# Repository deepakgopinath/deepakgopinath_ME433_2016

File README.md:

# deepakgopinath_ME433_2016
Repository for ME433 - Advanced Mechatronics Course (Spring 2016).

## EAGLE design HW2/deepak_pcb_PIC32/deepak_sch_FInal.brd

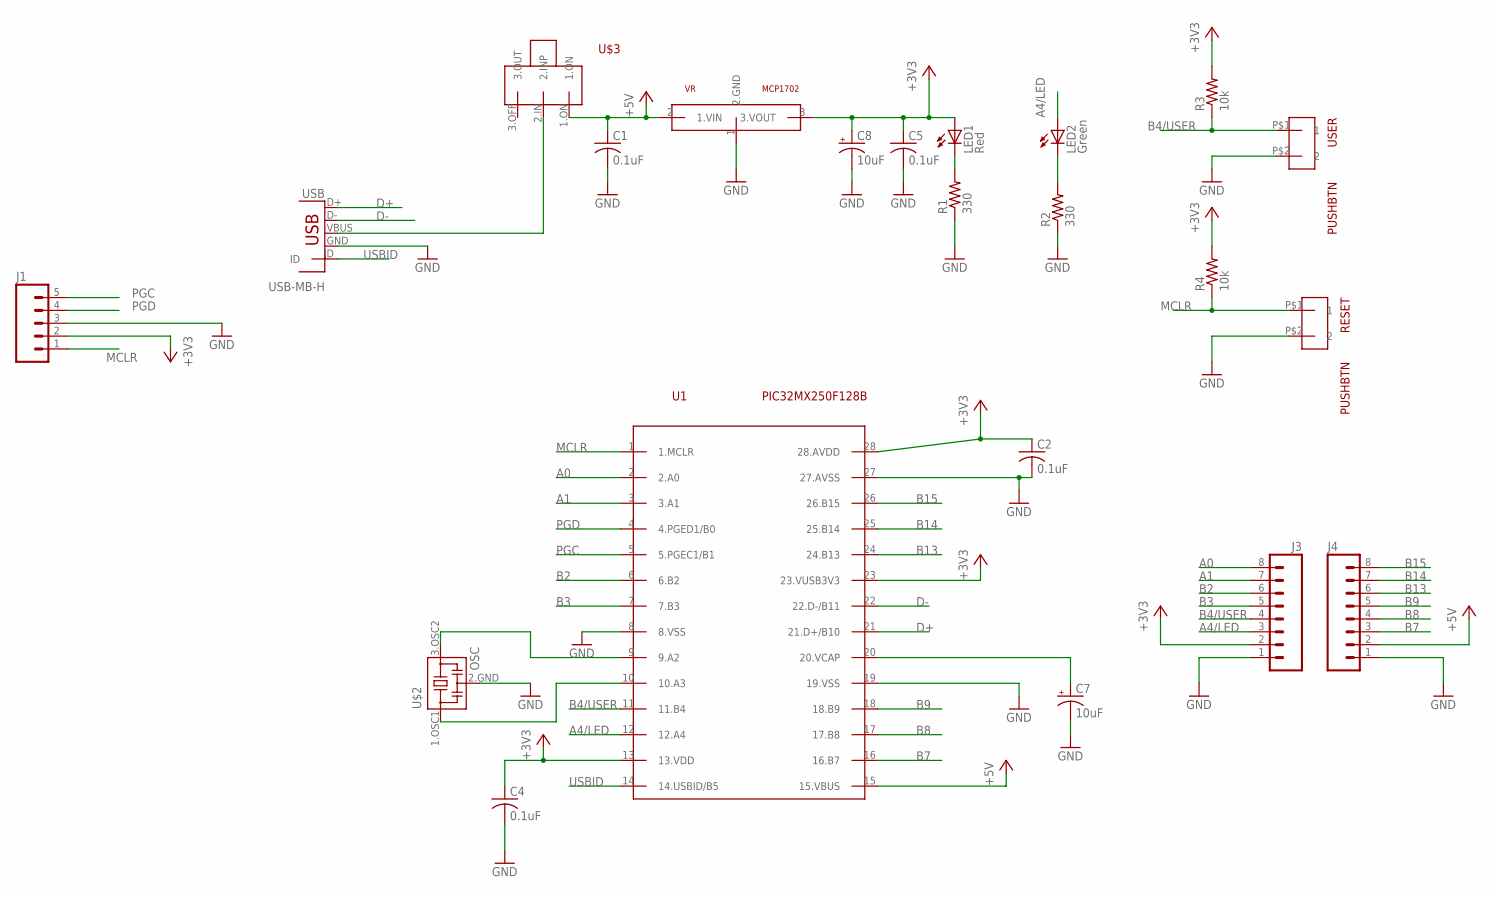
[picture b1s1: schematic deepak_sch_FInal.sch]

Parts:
C1, C2, C4, C5: 0.1uF; C025-024X044
C7, C8: 10uF; B45181A
J1: M05PTH; 1X05
J3, J4: M08; 1X08_ROUND
LED1: Red; LED3MM
LED2: Green; LED3MM
R1, R2: 330; 0207/10
R3, R4: 10k; 0207/10
RESET: PUSHBTN
U1: PIC32MX250F128B; DIL28-3
U$2: OSC
U$3: SLIDESWITCH
USB: USB-MB-H
USER: PUSHBTN
VR: MCP1702; TO92

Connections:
+3V3: C2.1, C4.1, C5.1, C8.+, J1.2, J3.2, LED1.A, R3.2, R4.2, U1.13 (13.VDD), U1.23 (23.VUSB3V3), U1.28 (28.AVDD), VR.3 (3.VOUT)
+5V: C1.1, J4.2, U1.15 (15.VBUS), U$3.1.ON, VR.2 (1.VIN)
A0: J3.8, U1.2 (2.A0)
A1: J3.7, U1.3 (3.A1)
A4/LED: J3.3, LED2.A, U1.12 (12.A4)
B2: J3.6, U1.6 (6.B2)
B3: J3.5, U1.7 (7.B3)
B4/USER: J3.4, R3.1, U1.11 (11.B4), USER.P$1 (1)
B7: J4.3, U1.16 (16.B7)
B8: J4.4, U1.17 (17.B8)
B9: J4.5, U1.18 (18.B9)
B13: J4.6, U1.24 (24.B13)
B14: J4.7, U1.25 (25.B14)
B15: J4.8, U1.26 (26.B15)
D+: U1.21 (21.D+/B10), USB.D+
D-: U1.22 (22.D-/B11), USB.D-
GND: C1.2, C2.2, C4.2, C5.2, C7.-, C8.-, J1.3, J3.1, J4.1, R1.1, R2.1, RESET.P$2 (2), U1.8 (8.VSS), U1.19 (19.VSS), U1.27 (27.AVSS), U$2.2.GND (2), USB.GND, USER.P$2 (2), VR.1 (2.GND)
MCLR: J1.1, R4.1, RESET.P$1 (1), U1.1 (1.MCLR)
unnamed: U1.9 (9.A2), U$2.3.OSC2 (3)
unnamed: U1.10 (10.A3), U$2.1.OSC1 (1)
unnamed: U$3.2.IN (2.INP), USB.VBUS
unnamed: LED2.K (C), R2.2
unnamed: LED1.K (C), R1.2
unnamed: C7.+, U1.20 (20.VCAP)
PGC: J1.5, U1.5 (5.PGEC1/B1)
PGD: J1.4, U1.4 (4.PGED1/B0)
USBID: U1.14 (14.USBID/B5), USB.ID

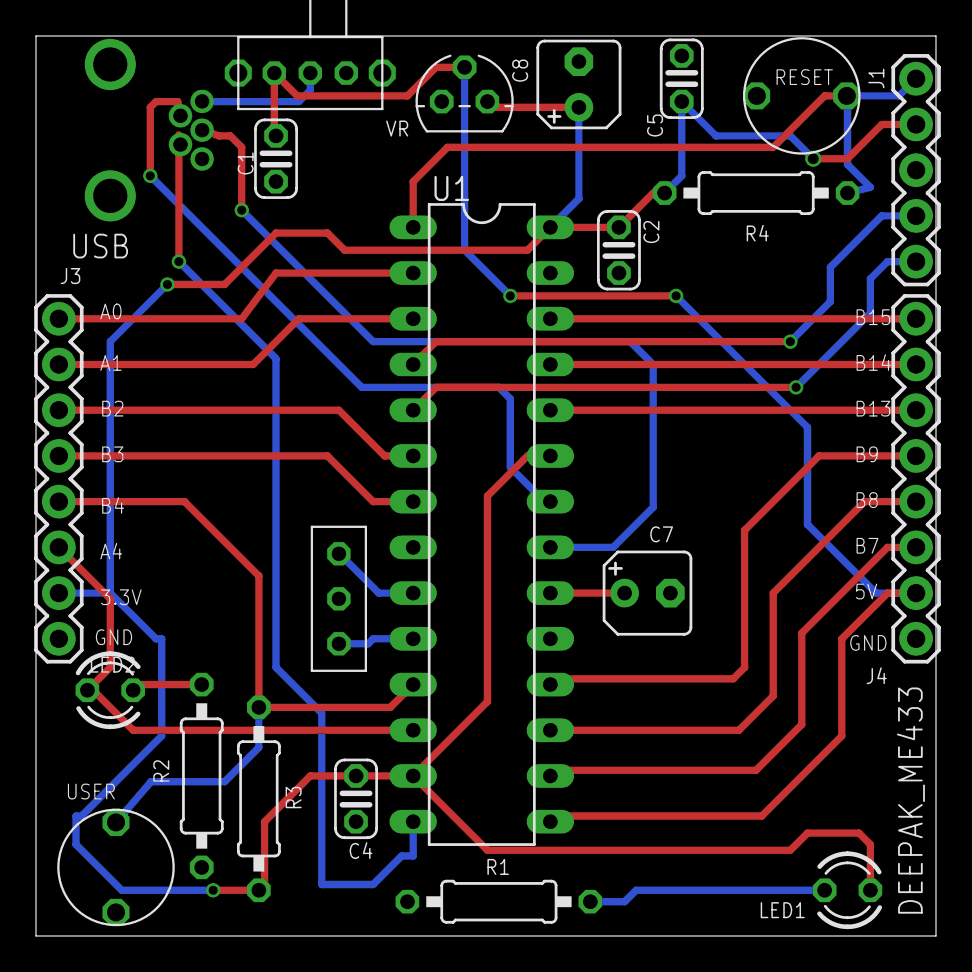
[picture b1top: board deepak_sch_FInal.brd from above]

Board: 2 copper layers, 50.0 x 50.0 mm, 22 parts (0 on the bottom side), 27 nets.

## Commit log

2016-04-03 Circuit diagram added
2016-04-03 Finished breadboard. Pictures
2016-04-03 Created MPLAB project. Added main.c
2016-04-04 Green LED at 1000Mhz. No user reset yet.1000Mhz nScope plot added
2016-04-04 Added user button functionality. Upon pressing, the LED goes off. Upon releasing the 1000Mhz toggle resumes
2016-04-05 Homework 2 started
2016-04-07 Made eagle library
2016-04-07 First pass at schematic. Push buttons and side switch left
2016-04-10 Second attempt at schematic
2016-04-10 Second attempt at schematic.Completed
2016-04-11 Second schematic. Small edits.
2016-04-13 Final Schematic. No long connections
2016-04-14 Error checked.
2016-04-14 Ready to be checked before order.
2016-04-20 HW4 SPI - started
2016-04-20 SPI done
2016-04-20 Started I2c and expander
2016-04-20 Finished I2c expander
2016-04-20 Added pictures
2016-04-24 IMU HW5 done. Accidently named it HW5 instead of HW4
2016-04-26 IMU HW - as specified in the wiki.
2016-05-09 LCD homework
2016-05-15 Android Hello World
2016-05-23 Android projects
2016-05-31 More homeworks
2016-06-09 Final commit
